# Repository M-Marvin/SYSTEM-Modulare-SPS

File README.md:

# SYSTEM-Modulare-SPS
Eine Modulares SPS System aus einem Raspberry Pi und ATmega328 Microcontrolern

Das Projekt ist noch nicht fertig, aber auf einem Steckbrett hat es schon funktioniert!

WISCHTIG: Datei wird auf der GitHub Webseite verbuggt angezeigt, besser runterladen und mit standart Texteditor öffnen!

-----------------------------------------------------------------------------------------------------

Die Modulare SPS besteht aus einem Raspberry Pi. der über ein Adaptermodul und
einem Flachbandkabel mit den einzelnen Modulen verbunden wird.

Die Moduel bestehen aus auf Hut-Schienen anbringbaren 3D-Gedruckten Gehäusen mit
entsprechenden Schaltungen darin.

Bisherige Module:
  - keine

In Entwiklung:
  - DO_16_R230  16 x Digitalausgang mit 230V Relay-Wechlerkontakten

Geplante Module:
  - DI_16_D24   16 x Digitaleingang 24V direkt gekoppelt (keine Relays dazwischen)
  - AI_1_D0-24  1 x Analogeingang 0V-24V direkt gekoppelt
  - AO_1_D0-24 1 x Analogausgang 0V-24V direkt gekoppelt (benötigt 24V Spannungsversorgung)

-----------------------------------------------------------------------------------------------------

Kurzbezeichnungs-Legende:

Beispiel: DO - 16 - R230

D = Digital (1 oder 0 / Ein oder Aus)
O = Output (Ausgang)

16 = Schnittstelle 16 mal vorhanden

R = Relay/Galvanisch getrennt
230 = Maximale Spannung 230V

Zusammensetzung: [Art der Schnittstelle] [Eingang/Ausgang*] _ [Anzahl der Schnittstellen] _ [Kopplungsart] [Maximal-Spannung/Spannungsbereich]
* (oder weggelassen wenn nicht klar definierbar, z.B: bei Netzwerk)

[Art der Schnittstelle]
- D Digital
- A Analog
- B Bus-System (zu Zeit noch nicht verwended, z.B. Netzwerk, D-Sub, MPI, ISP, USB, usw.)

[Eingang/Ausgang]
- I Eingang
- O Ausgang

[Kopplungsart]
- R Relay/Galvanisch getrennt
- D Direkt gekoppelt (GND der Leiterplatte/SPS und GND der Externen Anschlüsse sind identisch)

-----------------------------------------------------------------------------------------------------

Das projekt besteht aus:
- Raspberry Pi SPS Hauptprogramm (Dort wird das Programm der Steuerung und die Einstellung der Module reingeladen)
- ATmega Modul-Programme (Programme der jeweiligen Module)
- Schaltpläne/Leiterplatten entwürfe
- 3D-Druck Modelle für Gehäuse/Halterungen

Das Raspberry Pi Programm läuft mit der Bibliothek pi4j auf jedem kompatiblen Raspebrry Pi.
Die Datei wird einfach auf das Pi kopiert und über einen der folgenden Befehle gestartet:
    sudo java -jar *Pfad der Jar*               um das SPS Programm zu starten
    sudo java -jar *Pfad der Jar* -configMode   um den System-Konfigurator zu starten und die Adressen der Module fest zu legen

Die ATmega Programme werden als .hex (Textdatei mit Hexadezimal-Codes) compiliert und per SPI in den Controler geladen.

-----------------------------------------------------------------------------------------------------

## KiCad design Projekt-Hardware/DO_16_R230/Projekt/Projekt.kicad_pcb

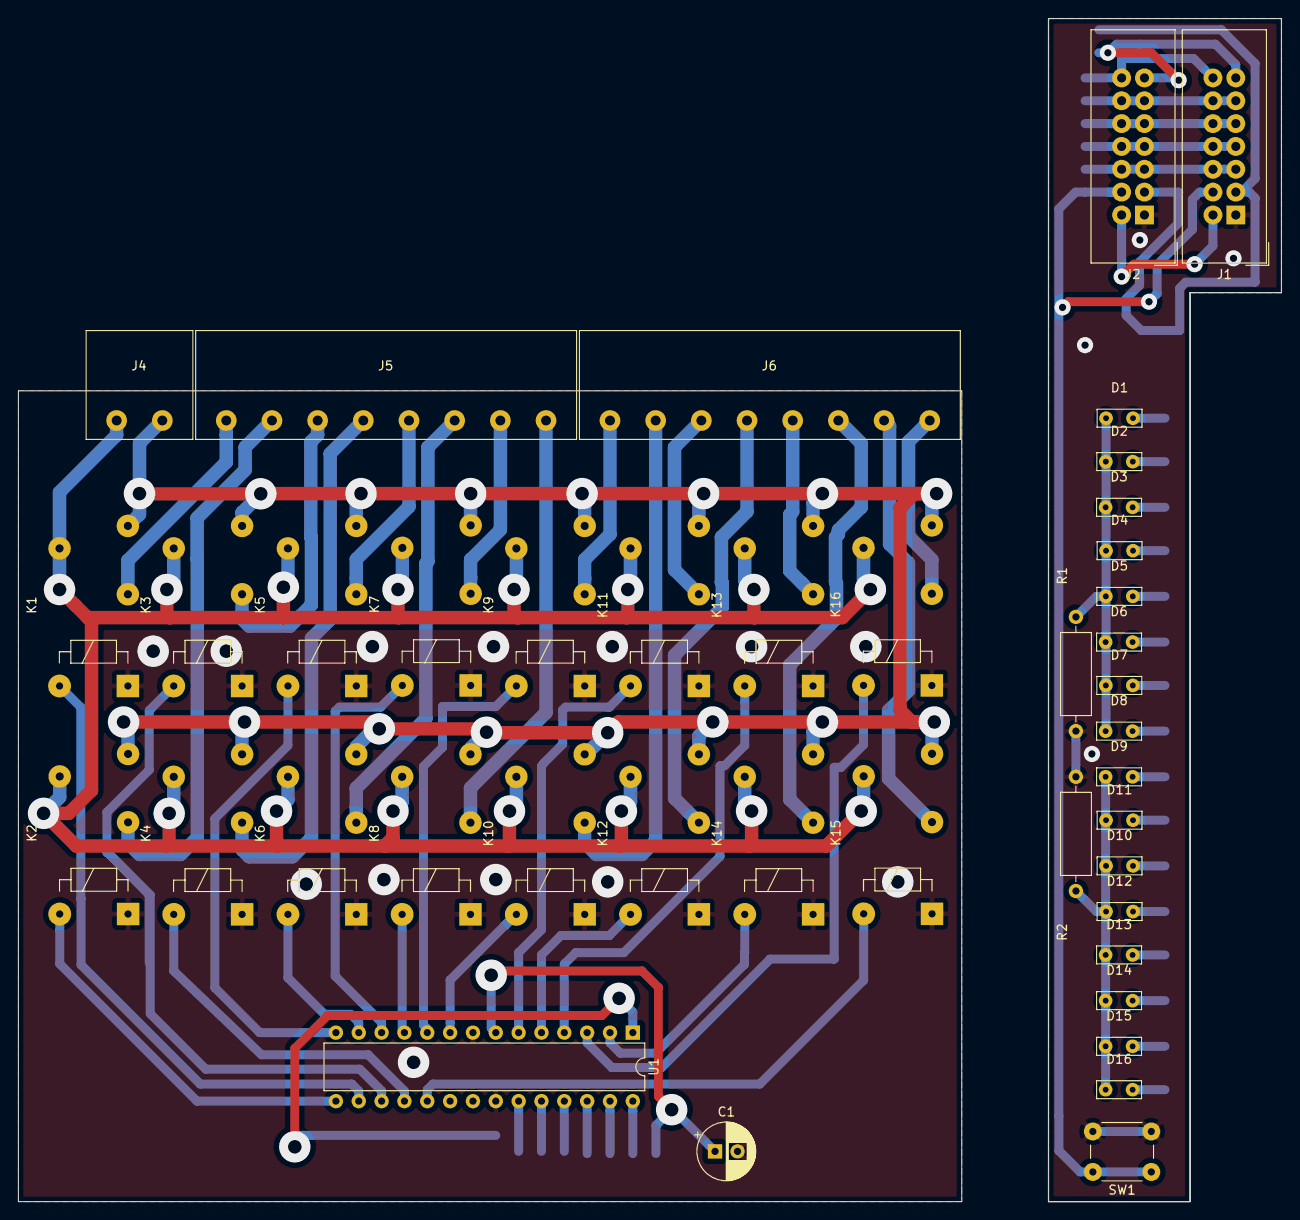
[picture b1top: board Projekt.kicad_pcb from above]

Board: 2 copper layers, 140.5 x 131.6 mm, 42 parts (0 on the bottom side), 46 nets.

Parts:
C1: 10uF; CP_Radial_D6.3mm_P2.50mm
D1, D2, D3, D4, D5, D6, D7, D8, D9, D10, D11, D12, D13, D14, D15, D16: LED; LED_5x2mm
J1, J2: COM_Bus; IDC-Header_2x07_P2.54mm_Vertical
J4: Conn_01x02; RND_Steckklemme_2
J5, J6: Conn_01x08; RND_Steckklemme_8
K1, K2, K3, K4, K5, K6, K7, K8, K9, K10, K11, K12, K13, K14, K15, K16: DIPxx-1Cxx-51x; Relay_1-Form-C-20,6x10,2mm
R1, R2: 220R; R_Axial_DIN0309_L9.0mm_D3.2mm_P12.70mm_Horizontal
SW1: RESET; SW_PUSH_6mm_H8mm
U1: ATmega328P-PU; DIP-28_W7.62mm

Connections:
/+5V: C1.1, J1.2, J2.2, U1.7
/-5V: J1.3, J2.3
/CLOCK: J1.13, J2.13, U1.27
/COM_IN_1: J1.5, J1.6, J2.5, J2.6, U1.25
/COM_IN_2: J1.7, J1.8, J2.7, J2.8, U1.26
/COM_OUT_1: J1.9, J1.10, J2.9, J2.10, U1.23
/COM_OUT_2: J1.11, J1.12, J2.11, J2.12, U1.24
/ENABLE: J1.14, J2.14, U1.28
/GND: C1.2, J1.1, J2.1, K1.6, K2.6, K3.6, K4.6, K5.6, K6.6, K7.6, K8.6, K9.6, K10.6, K11.6, K12.6, K13.6, K14.6, K15.6, K16.6, R1.2, R2.2, SW1.0,82, SW1.2, U1.8, U1.22
/RESET: J1.4, J2.4, SW1.0,81, SW1.1, U1.1
unnamed: D1.1, D2.1, D3.1, D4.1, D5.1, D6.1, D7.1, D8.1, R1.1
unnamed: D1.2, K1.2, U1.16
unnamed: D2.2, K2.2, U1.15
unnamed: D3.2, K3.2, U1.17
unnamed: D4.2, K4.2, U1.18
unnamed: D5.2, K5.2, U1.14
unnamed: D6.2, K6.2, U1.13
unnamed: D7.2, K7.2, U1.12
unnamed: D8.2, K8.2, U1.11
unnamed: D9.2, K9.2, U1.10
unnamed: D9.1, D10.1, D11.1, D12.1, D13.1, D14.1, D15.1, D16.1, R2.1
unnamed: D10.2, K10.2, U1.9
unnamed: D11.2, K11.2, U1.6
unnamed: D12.2, K12.2, U1.5
unnamed: D13.2, K13.2, U1.4
unnamed: D14.2, K14.2, U1.2
unnamed: D15.2, K15.2, U1.19
unnamed: D16.2, K16.2, U1.3
unnamed: J4.1, K1.1, K2.1, K3.1, K4.1, K5.1, K6.1, K7.1, K8.1, K9.1, K10.1, K11.1, K12.1, K13.1, K14.1, K15.1, K16.1
unnamed: J4.2, K1.14, K2.14, K3.14, K4.14, K5.14, K6.14, K7.14, K8.14, K9.14, K10.14, K11.14, K12.14, K13.14, K14.14, K15.14, K16.14
unnamed: J5.1, K1.7
unnamed: J5.2, K2.7
unnamed: J5.3, K3.7
unnamed: J5.4, K4.7
unnamed: J5.5, K5.7
unnamed: J5.6, K6.7
unnamed: J5.7, K7.7
unnamed: J5.8, K8.7
unnamed: J6.1, K9.7
unnamed: J6.2, K10.7
unnamed: J6.3, K11.7
unnamed: J6.4, K12.7
unnamed: J6.5, K13.7
unnamed: J6.6, K14.7
unnamed: J6.7, K15.7
unnamed: J6.8, K16.7

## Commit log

2020-12-07 Hochladen des Aktuellen Projekt-Stands
    Raspberry:
    - Java-Software zum betrieb der Steuerung
    - Netzwerk fähig
    - GPIO/Module (Ein/Ausgänge) noch nicht implementiert
    ATmega:
    - Software für DO_16_R230 (16x230V Relay-Ausgänge) Modul
2020-12-11 IOSystem updated
    Senden von Daten zu den Modulen fertig.
    Empfangen von Daten von den Modulen angefangen.
    SPS-Syste-Configurator hinzugefügt um Adressen zu vergeben.
2020-12-16 Modul-Kommunikation fertig
    Protokoll zur Kommunikation zwischen
    ATmega und Raspberry Pi fertig gestellt.
    (Änderungen kommen eventuell noch)
2020-12-16 EEPROM Speicher für Modul Adresse
    Die Adresse des Moduls DO_16_R230 wird
    jetzt bei Ein/Aus schalten im EEPROM des ATmega328 gespeichert.
2020-12-17 Erster (meschanischer) Entwurf für DO_16_R230 Modul
    Erster Entwurf für meschanische Bauteile des
    DO_16_R230 Moduls:
    - Entwurf für Leiterplatten
    Fehlende Entwürfe:
    - Gehäuse
    - Halterungen
2020-12-17 BugFix PortState Abfrage DO_16_R230 Modul
    PORT Angaben bei der Abfrage der Ausgangszustände korigiert.
    Unnötiges "Testprojekt" gelöcht (GccApplication1).
2020-12-18 Gehäuse für DO_16_R230 begonnen
    Angefangen Gehäuse für DO_16_R230
    angefangen zu entwerfen.
2020-12-19 BugFix bei 3D Modells
    Fehler in den 3D Modellen behoben.
    Sie können jetzt gedruckt werden.
2020-12-19 Korrektur im Schaltplan
    RESET Taster auf von +5V auf GND verschoben.
2020-12-26 Anpassungen Gehäuse + CNC Experimente
    Anpassungen des Gehäuses an die Leiteplatte
    Angefangen mit Tests für das herstellen der Leiterplatte mit einer CNC Fräse
2021-02-25 Hardware CNC Codes erstellt
    Fertigungsdateien für eine CNC Version der
    Leiterplatten erstellt.
